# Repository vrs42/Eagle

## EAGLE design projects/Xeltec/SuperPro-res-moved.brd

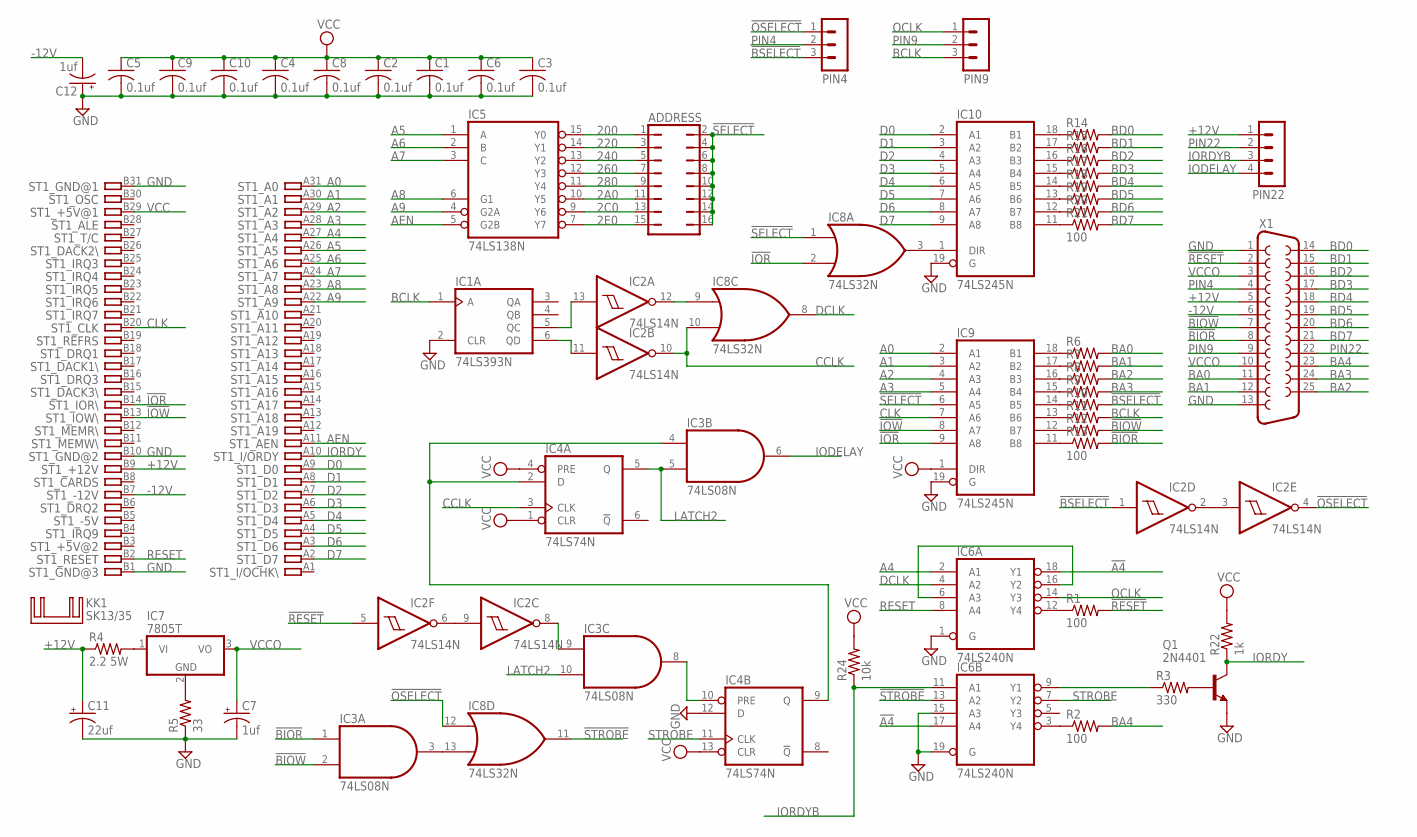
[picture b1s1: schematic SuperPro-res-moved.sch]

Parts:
ADDRESS: JP8Q
C1, C2, C3, C4, C5, C6, C8, C9, C10: 0.1uf; C050-025X075
C7, C12: 1uf; E5-10,5
C11: 22uf; E5-10,5
IC1: 74LS393N; DIL14
IC2: 74LS14N; DIL14
IC3: 74LS08N; DIL14
IC4: 74LS74N; DIL14
IC5: 74LS138N; DIL16
IC6: 74LS240N; DIL20
IC7: 7805T; TO220H
IC8: 74LS32N; DIL14
IC9, IC10: 74LS245N; DIL20
KK1: SK13/35
PIN4, PIN9: MA03-1
PIN22: MA04-1
Q1: 2N4401; TO92
R1, R2, R13, R21: 100; 0207/10
R3: 330; 0207/10
R4: 2.2 5W; 0922/22
R5: 33; 0207/10
R6, R7, R8, R9, R10, R11, R12, R14, R15, R16, R17, R18, R19, R20: R-US_0207/10; 0207/10
R22: 1k; 0207/10
R24: 10k; 0207/10
ST1: IBM8BIT
X1: F25H

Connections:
2A0: ADDRESS.11, IC5.10 (Y5)
2C0: ADDRESS.13, IC5.9 (Y6)
2E0: ADDRESS.15, IC5.7 (Y7)
200: ADDRESS.1, IC5.15 (Y0)
220: ADDRESS.3, IC5.14 (Y1)
240: ADDRESS.5, IC5.13 (Y2)
260: ADDRESS.7, IC5.12 (Y3)
280: ADDRESS.9, IC5.11 (Y4)
!A4: IC6.17 (A4), IC6.18 (Y1)
!BIOR: IC3.1 (I0), R13.2, X1.8
!BIOW: IC3.2 (I1), R12.2, X1.7
!BSELECT: IC2.1 (I), PIN4.3, R10.2
!IOR: IC8.2 (I1), IC9.9 (A8), ST1.B14
!IOW: IC9.8 (A7), ST1.B13
!OSELECT: IC2.4 (O), IC8.12 (I0), PIN4.1
!RESET: IC2.5 (I), R1.2, X1.2
!SELECT: ADDRESS.2, ADDRESS.4, ADDRESS.6, ADDRESS.8, ADDRESS.10, ADDRESS.12, ADDRESS.14, ADDRESS.16, IC8.1 (I0), IC9.6 (A5)
!STROBE: IC6.13 (A2), IC8.11 (O)
+12V: C11.+, PIN22.1, R4.1, ST1.B9, X1.5
-12V: C12.-, ST1.B7, X1.6
A0: IC9.2 (A1), ST1.A31
A1: IC9.3 (A2), ST1.A30
A2: IC9.4 (A3), ST1.A29
A3: IC9.5 (A4), ST1.A28
A4: IC6.2 (A1), ST1.A27
A5: IC5.1 (A), ST1.A26
A6: IC5.2 (B), ST1.A25
A7: IC5.3 (C), ST1.A24
A8: IC5.6 (G1), ST1.A23
A9: IC5.4 (G2A), ST1.A22
AEN: IC5.5 (G2B), ST1.A11
BA0: R6.2, X1.11
BA1: R7.2, X1.12
BA2: R8.2, X1.25
BA3: R9.2, X1.24
BA4: R2.2, X1.23
BCLK: IC1.1 (A), PIN9.3, R11.2
BD0: R14.2, X1.14
BD1: R15.2, X1.15
BD2: R16.2, X1.16
BD3: R17.2, X1.17
BD4: R18.2, X1.18
BD5: R19.2, X1.19
BD6: R20.2, X1.20
BD7: R21.2, X1.21
CCLK: IC2.10 (O), IC4.3 (CLK), IC8.10 (I1)
CLK: IC9.7 (A6), ST1.B20
D0: IC10.2 (A1), ST1.A9
D1: IC10.3 (A2), ST1.A8
D2: IC10.4 (A3), ST1.A7
D3: IC10.5 (A4), ST1.A6
D4: IC10.6 (A5), ST1.A5
D5: IC10.7 (A6), ST1.A4
D6: IC10.8 (A7), ST1.A3
D7: IC10.9 (A8), ST1.A2
DCLK: IC6.4 (A2), IC8.8 (O)
GND: C1.2, C2.2, C3.2, C4.2, C5.2, C6.2, C7.-, C8.2, C9.2, C10.2, C11.-, C12.+, IC1.2 (CLR), IC1.7 (GND), IC2.7 (GND), IC3.7 (GND), IC4.7 (GND), IC4.12 (D), IC5.8 (GND), IC6.1 (G), IC6.10 (GND), IC6.15 (A3), IC6.19 (G), IC8.7 (GND), IC9.10 (GND), IC9.19 (G), IC10.10 (GND), IC10.19 (G), Q1.3 (E), R5.1, ST1.B1, ST1.B10, ST1.B31, X1.1, X1.13
IODELAY: IC3.6 (O), PIN22.4
IORDY: Q1.1 (C), R22.1, ST1.A10
IORDYB: IC6.11 (A1), PIN22.3, R24.1
LATCH2: IC3.5 (I1), IC3.10 (I1), IC4.5 (Q)
unnamed: IC8.3 (O), IC10.1 (DIR)
unnamed: IC7.2 (GND), R5.2
unnamed: IC10.13 (B6), R19.1
unnamed: IC10.17 (B2), R15.1
unnamed: IC10.16 (B3), R16.1
unnamed: IC10.15 (B4), R17.1
unnamed: IC10.14 (B5), R18.1
unnamed: IC10.12 (B7), R20.1
unnamed: IC10.11 (B8), R21.1
unnamed: IC10.18 (B1), R14.1
unnamed: IC9.18 (B1), R6.1
unnamed: IC9.17 (B2), R7.1
unnamed: IC9.16 (B3), R8.1
unnamed: IC9.15 (B4), R9.1
unnamed: IC9.14 (B5), R10.1
unnamed: IC9.13 (B6), R11.1
unnamed: IC9.12 (B7), R12.1
unnamed: IC9.11 (B8), R13.1
unnamed: IC6.12 (Y4), R1.1
unnamed: IC2.6 (O), IC2.9 (I)
unnamed: IC2.2 (O), IC2.3 (I)
unnamed: IC1.6 (QD), IC2.11 (I)
unnamed: IC6.3 (Y4), R2.1
unnamed: IC1.5 (QC), IC2.13 (I)
unnamed: IC7.1 (VI), R4.2
unnamed: IC2.12 (O), IC8.9 (I0)
unnamed: IC6.6 (A3), IC6.16 (Y2)
unnamed: IC3.3 (O), IC8.13 (I1)
unnamed: IC3.4 (I0), IC4.2 (D), IC4.9 (Q)
unnamed: IC6.9 (Y1), R3.1
unnamed: IC3.8 (O), IC4.10 (PRE)
unnamed: IC2.8 (O), IC3.9 (I0)
unnamed: Q1.2 (B), R3.2
OCLK: IC6.14 (Y3), PIN9.1
PIN4: PIN4.2, X1.4
PIN9: PIN9.2, X1.9
PIN22: PIN22.2, X1.22
RESET: IC6.8 (A4), ST1.B2
STROBE: IC4.11 (CLK), IC6.7 (Y2)
VCC: C1.1, C2.1, C3.1, C4.1, C5.1, C6.1, C8.1, C9.1, C10.1, IC1.14 (VCC), IC2.14 (VCC), IC3.14 (VCC), IC4.1 (CLR), IC4.4 (PRE), IC4.13 (CLR), IC4.14 (VCC), IC5.16 (VCC), IC6.20 (VCC), IC8.14 (VCC), IC9.1 (DIR), IC9.20 (VCC), IC10.20 (VCC), R22.2, R24.2, ST1.B29
VCCO: C7.+, IC7.3 (VO), X1.3, X1.10

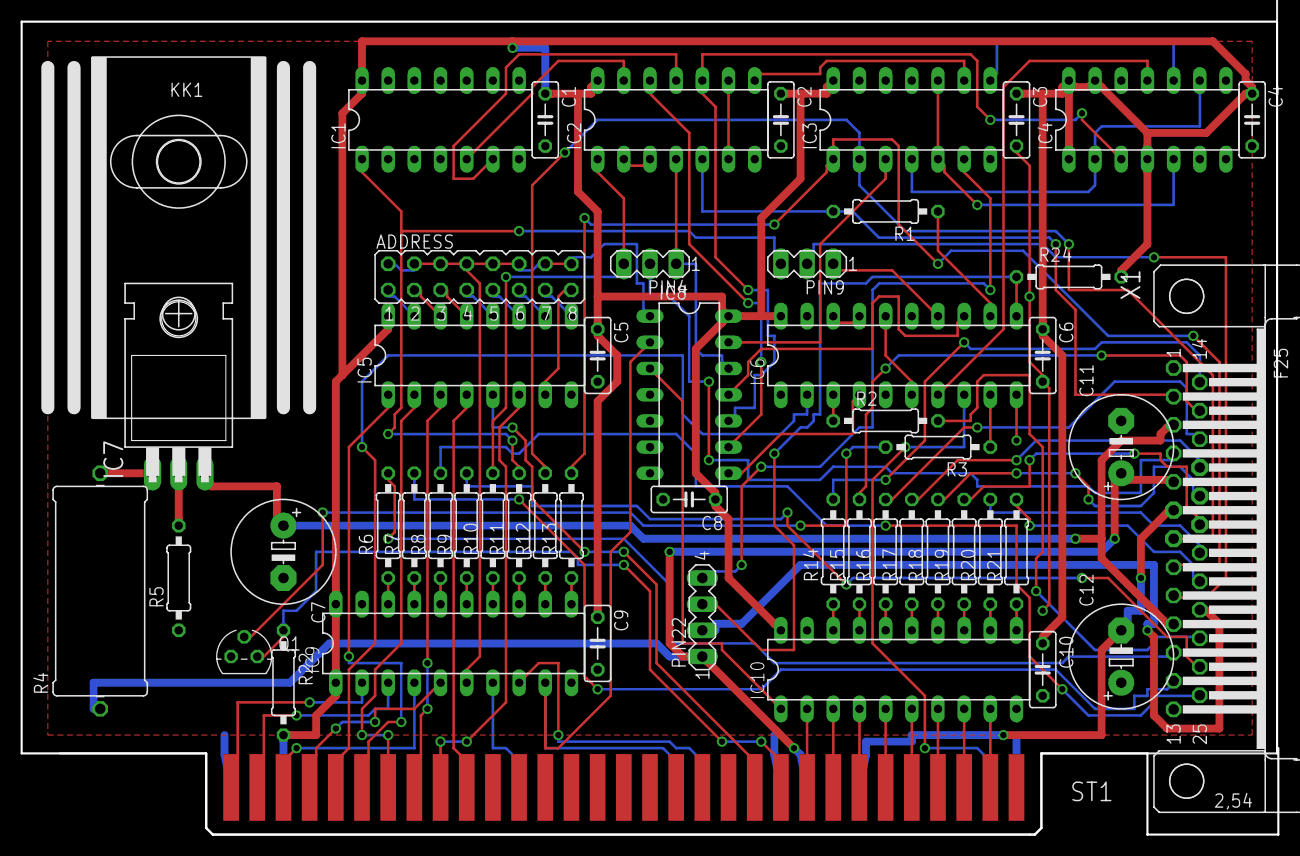
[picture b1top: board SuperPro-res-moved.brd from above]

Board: 2 copper layers, 121.9 x 78.9 mm, 54 parts (0 on the bottom side), 102 nets.

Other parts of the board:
U$1: 4,1

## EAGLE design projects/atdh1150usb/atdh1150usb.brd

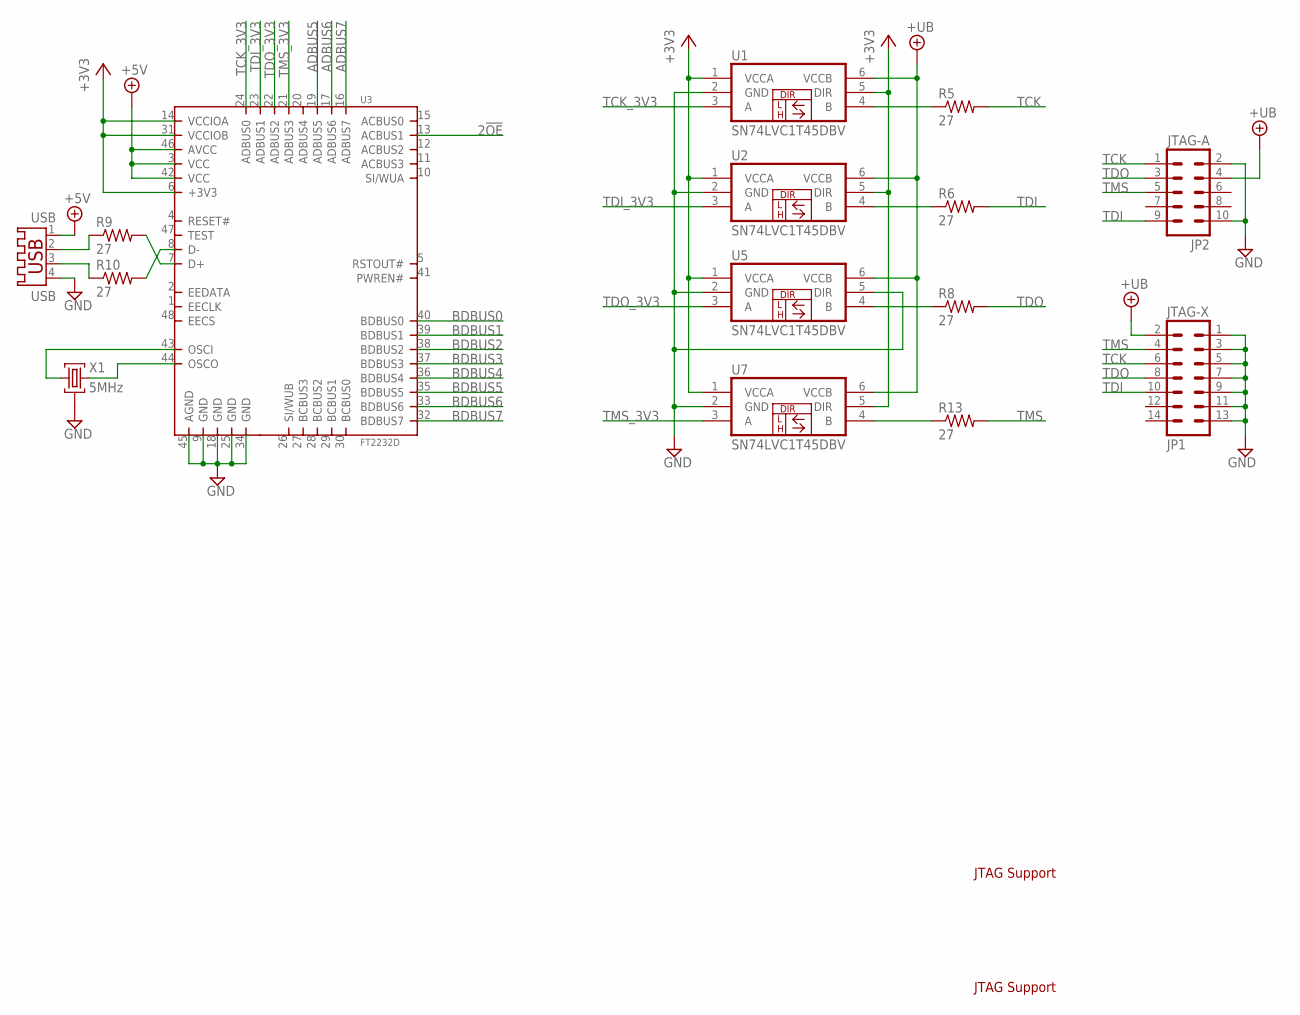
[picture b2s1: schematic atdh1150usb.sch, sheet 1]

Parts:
JP1: JTAG-X; ML14
JP2: JTAG-A; ML10
R5, R6, R8, R9, R10, R13: 27; R0805
U1, U2, U5, U7: SN74LVC1T45DBV; DBV-R-PDSO-G6
U3: FT2232D; LQFP48
USB: USB; USB-A003
X1: 5MHz; HC49U

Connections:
2!OE: U3.13 (ACBUS1); also elsewhere on the board
+3V3: U1.1 (VCCA), U1.5 (DIR), U2.1 (VCCA), U2.5 (DIR), U3.6 (+3V3), U3.14 (VCCIOA), U3.31 (VCCIOB), U5.1 (VCCA), U7.1 (VCCA), U7.5 (DIR); also elsewhere on the board
+5V: U3.3 (VCC), U3.42 (VCC), U3.46 (AVCC), USB.1
+UB: JP1.2, JP2.4, U1.6 (VCCB), U2.6 (VCCB), U5.6 (VCCB), U7.6 (VCCB)
ADBUS5: U3.19 (ADBUS5); also elsewhere on the board
ADBUS6: U3.17 (ADBUS6); also elsewhere on the board
ADBUS7: U3.16 (ADBUS7); also elsewhere on the board
BDBUS0: U3.40 (BDBUS0); also elsewhere on the board
BDBUS1: U3.39 (BDBUS1); also elsewhere on the board
BDBUS2: U3.38 (BDBUS2); also elsewhere on the board
BDBUS3: U3.37 (BDBUS3); also elsewhere on the board
BDBUS4: U3.36 (BDBUS4); also elsewhere on the board
BDBUS5: U3.35 (BDBUS5); also elsewhere on the board
BDBUS6: U3.33 (BDBUS6); also elsewhere on the board
BDBUS7: U3.32 (BDBUS7); also elsewhere on the board
GND: JP1.1, JP1.3, JP1.5, JP1.7, JP1.9, JP1.11, JP1.13, JP2.2, JP2.10, U1.2 (GND), U2.2 (GND), U3.9 (GND), U3.18 (GND), U3.25 (GND), U3.34 (GND), U3.45 (AGND), U5.2 (GND), U5.5 (DIR), U7.2 (GND), USB.4, X1.2; also elsewhere on the board
unnamed: R9.1, USB.2
unnamed: R10.1, USB.3
unnamed: R10.2, U3.8 (D-)
unnamed: R9.2, U3.7 (D+)
unnamed: U3.44 (OSCO), X1.3
unnamed: U3.43 (OSCI), X1.1
unnamed: R5.1, U1.4 (B)
unnamed: R6.1, U2.4 (B)
unnamed: R8.1, U5.4 (B)
unnamed: R13.1, U7.4 (B)
TCK: JP1.6, JP2.1, R5.2
TCK_3V3: U1.3 (A), U3.24 (ADBUS0); also elsewhere on the board
TDI: JP1.10, JP2.9, R6.2
TDI_3V3: U2.3 (A), U3.23 (ADBUS1); also elsewhere on the board
TDO: JP1.8, JP2.3, R8.2
TDO_3V3: U3.22 (ADBUS2), U5.3 (A); also elsewhere on the board
TMS: JP1.4, JP2.5, R13.2
TMS_3V3: U3.21 (ADBUS3), U7.3 (A); also elsewhere on the board

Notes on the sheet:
JTAG Support

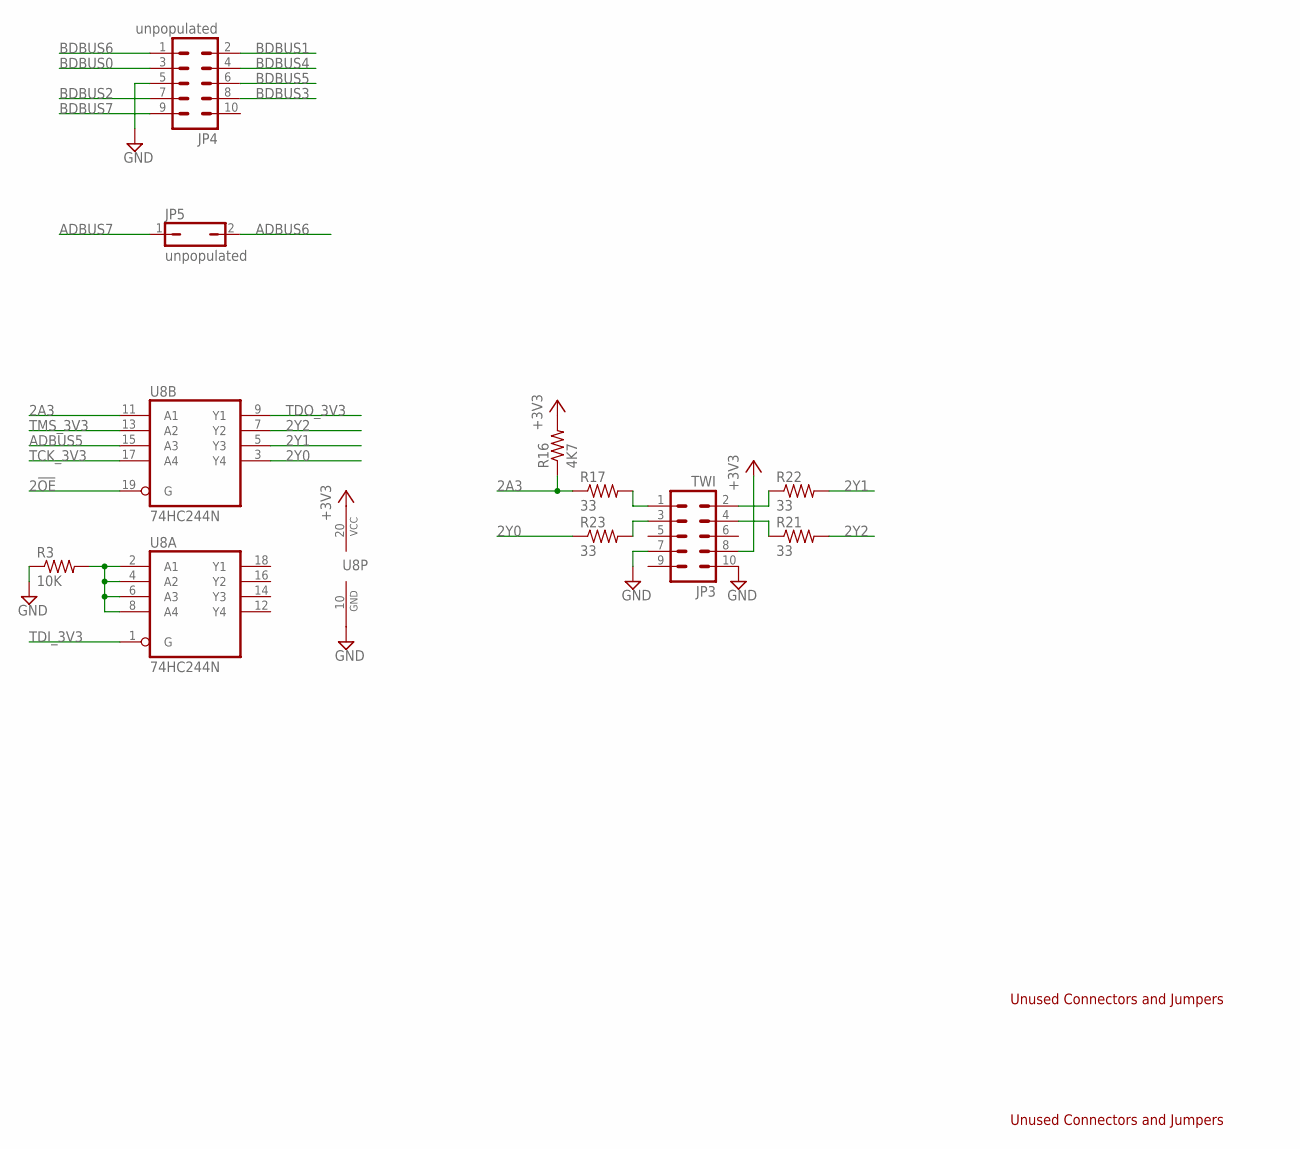
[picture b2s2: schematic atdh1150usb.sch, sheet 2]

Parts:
JP3: TWI; ML10
JP4: unpopulated; ML10
JP5: unpopulated; JP1
R3: 10K; R0805
R16: 4K7; R0805
R17, R21, R22, R23: 33; R0805
U8: 74HC244N; DIL20

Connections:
2!OE: U8.19 (G); also elsewhere on the board
2A3: R16.1, R17.1, U8.11 (A1)
2Y0: R23.1, U8.3 (Y4)
2Y1: R22.2, U8.5 (Y3)
2Y2: R21.2, U8.7 (Y2)
+3V3: JP3.8, R16.2, U8.20 (VCC); also elsewhere on the board
ADBUS5: U8.15 (A3); also elsewhere on the board
ADBUS6: JP5.2; also elsewhere on the board
ADBUS7: JP5.1; also elsewhere on the board
BDBUS0: JP4.3; also elsewhere on the board
BDBUS1: JP4.2; also elsewhere on the board
BDBUS2: JP4.7; also elsewhere on the board
BDBUS3: JP4.8; also elsewhere on the board
BDBUS4: JP4.4; also elsewhere on the board
BDBUS5: JP4.6; also elsewhere on the board
BDBUS6: JP4.1; also elsewhere on the board
BDBUS7: JP4.9; also elsewhere on the board
GND: JP3.7, JP3.10, JP4.5, R3.1, U8.10 (GND); also elsewhere on the board
unnamed: JP3.3, R23.2
unnamed: JP3.1, R17.2
unnamed: R3.2, U8.2 (A1), U8.4 (A2), U8.6 (A3), U8.8 (A4)
unnamed: JP3.2, R22.1
unnamed: JP3.4, R21.1
TCK_3V3: U8.17 (A4); also elsewhere on the board
TDI_3V3: U8.1 (G); also elsewhere on the board
TDO_3V3: U8.9 (Y1); also elsewhere on the board
TMS_3V3: U8.13 (A2); also elsewhere on the board

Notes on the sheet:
Unused Connectors and Jumpers

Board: 2 copper layers, 25 parts (0 on the bottom side), 43 nets, no tracks yet.

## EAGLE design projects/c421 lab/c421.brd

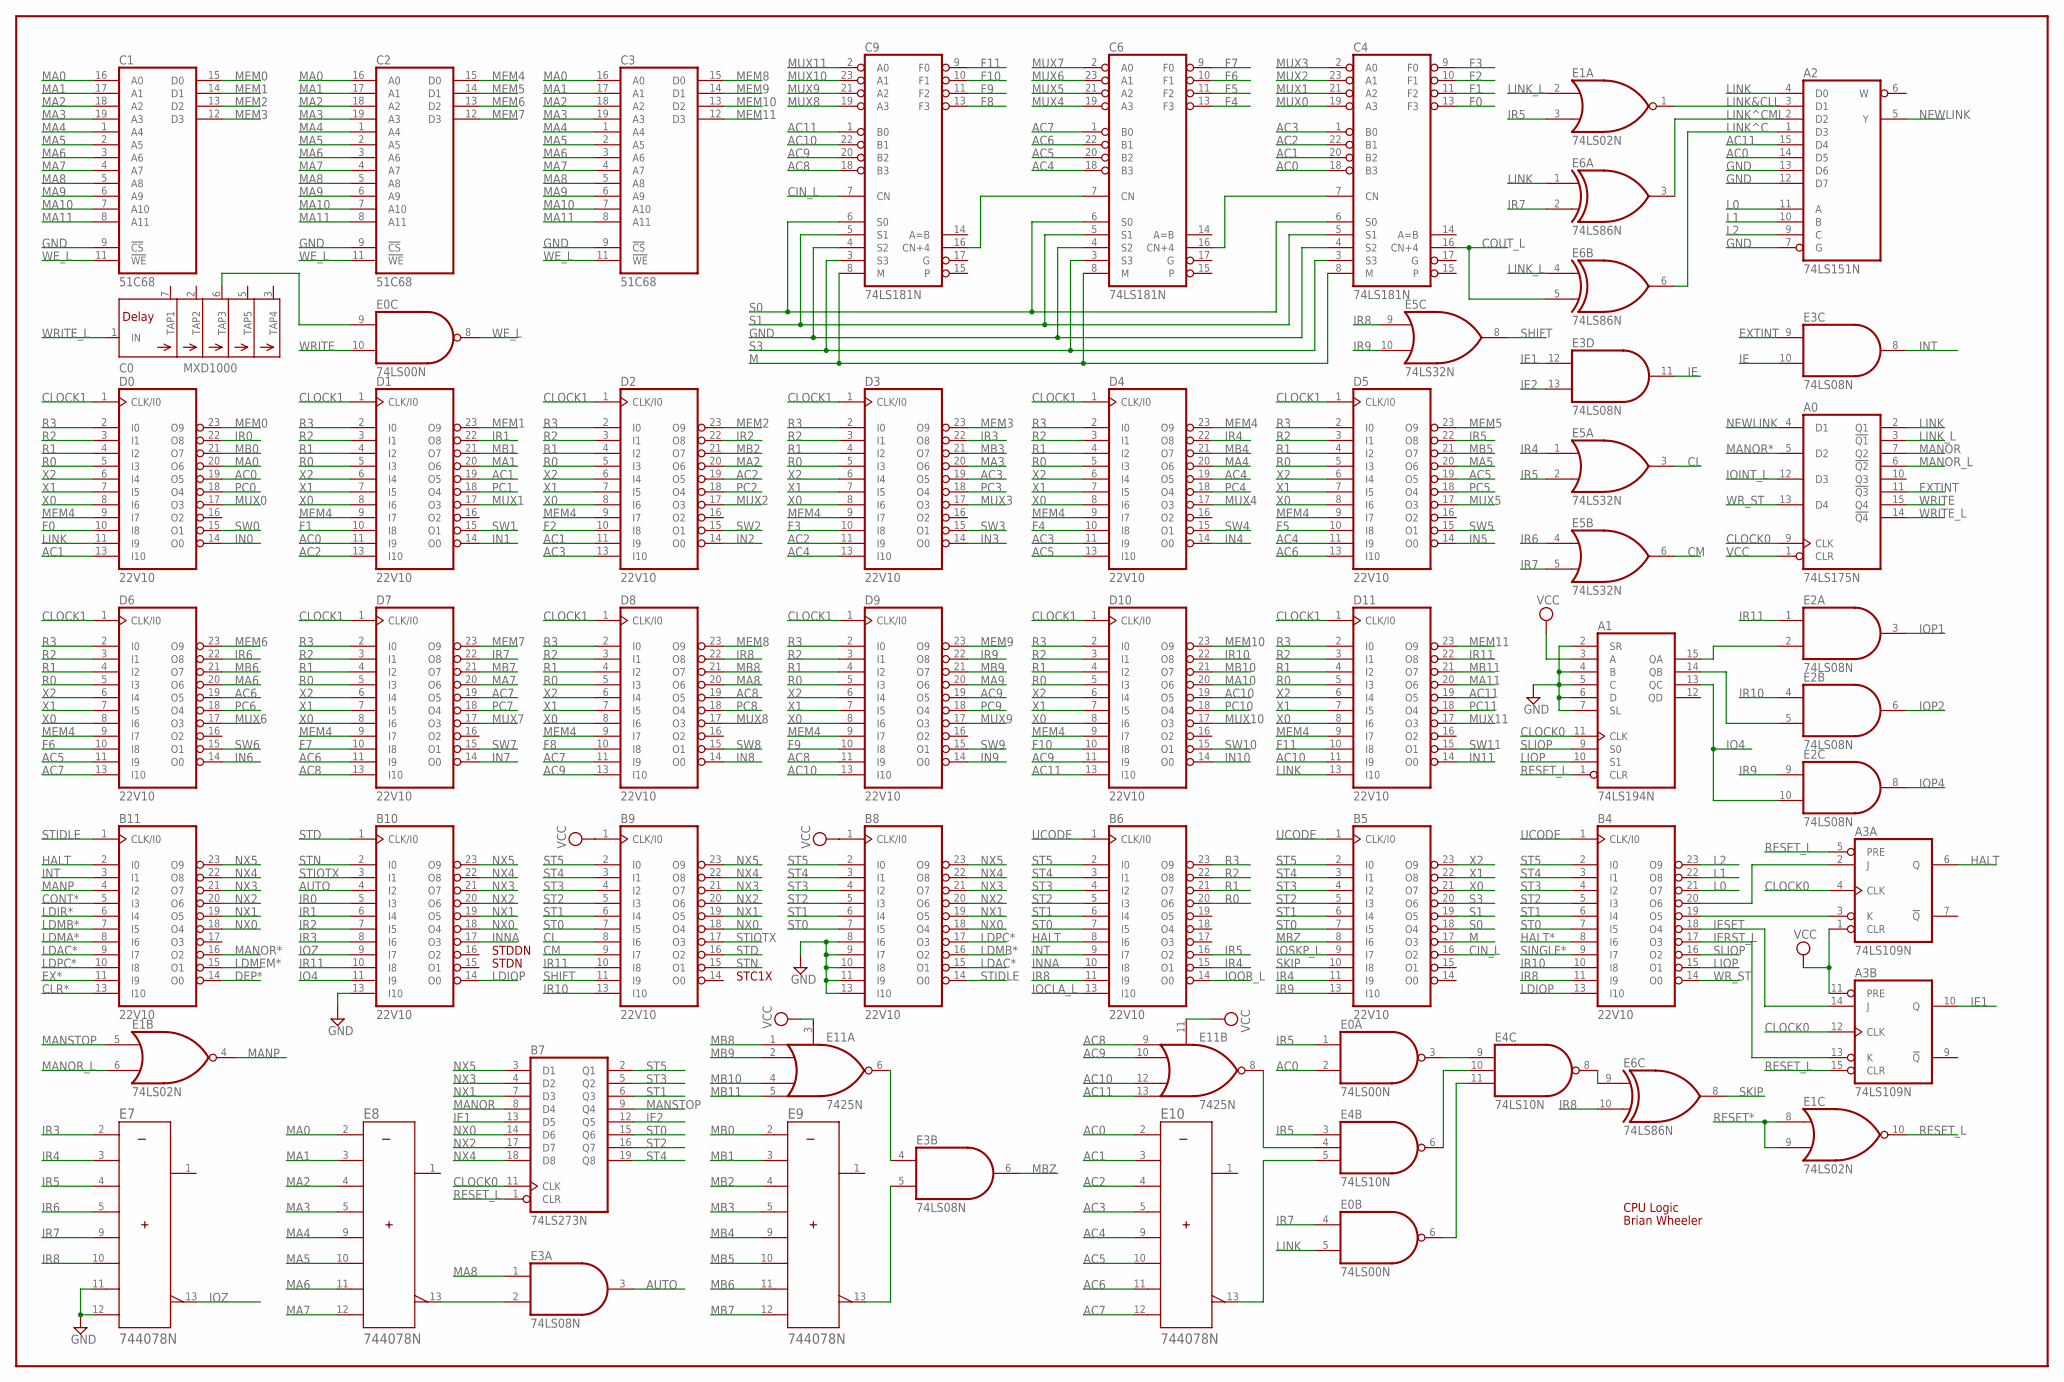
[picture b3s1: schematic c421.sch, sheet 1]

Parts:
A0: 74LS175N; DIL16
A1: 74LS194N; DIL16
A2: 74LS151N; DIL16
A3: 74LS109N; DIL16
B4, B5, B6, B8, B9, B10, B11: 22V10; DIL24-3
B7: 74LS273N; DIL20
C0: MXD1000; DIL08
C1, C2, C3: 51C68; DIL20
C4, C6, C9: 74LS181N; DIL24-6
D0, D1, D2, D3, D4, D5, D6, D7, D8, D9, D10, D11: 22V10; DIL24-3
E0: 74LS00N; DIL14
E1: 74LS02N; DIL14
E2, E3: 74LS08N; DIL14
E4: 74LS10N; DIL14
E5: 74LS32N; DIL14
E6: 74LS86N; DIL14
E7, E8, E9, E10: 744078N; DIL14
E11: 7425N; DIL14

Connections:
AC0: A2.14 (D5), C4.18 (B3), D0.19 (O5), D1.11 (I9), E0.2 (I1), E10.2 (A); also elsewhere on the board
AC1: C4.20 (B2), D0.13 (I10), D1.19 (O5), D2.11 (I9), E10.3 (B); also elsewhere on the board
AC2: C4.22 (B1), D1.13 (I10), D2.19 (O5), D3.11 (I9), E10.4 (C); also elsewhere on the board
AC3: C4.1 (B0), D2.13 (I10), D3.19 (O5), D4.11 (I9), E10.5 (D); also elsewhere on the board
AC4: C6.18 (B3), D3.13 (I10), D4.19 (O5), D5.11 (I9), E10.9 (E); also elsewhere on the board
AC5: C6.20 (B2), D4.13 (I10), D5.19 (O5), D6.11 (I9), E10.10 (F); also elsewhere on the board
AC6: C6.22 (B1), D5.13 (I10), D6.19 (O5), D7.11 (I9), E10.11 (G); also elsewhere on the board
AC7: C6.1 (B0), D6.13 (I10), D7.19 (O5), D8.11 (I9), E10.12 (H); also elsewhere on the board
AC8: C9.18 (B3), D7.13 (I10), D8.19 (O5), D9.11 (I9), E11.9 (I0); also elsewhere on the board
AC9: C9.20 (B2), D8.13 (I10), D9.19 (O5), D10.11 (I9), E11.10 (I1); also elsewhere on the board
AC10: C9.22 (B1), D9.13 (I10), D10.19 (O5), D11.11 (I9), E11.12 (I2); also elsewhere on the board
AC11: A2.15 (D4), C9.1 (B0), D10.13 (I10), D11.19 (O5), E11.13 (I3); also elsewhere on the board
AUTO: B10.4 (I2), E3.3 (O)
CIN_L: B5.16 (O2), C9.7 (CN); also elsewhere on the board
CL: B9.8 (I6), E5.3 (O)
CLOCK0: A0.9 (CLK), A1.11 (CLK), A3.4 (CLK), A3.12 (CLK), B7.11 (CLK); also elsewhere on the board
CLOCK1: D0.1 (CLK/I0), D1.1 (CLK/I0), D2.1 (CLK/I0), D3.1 (CLK/I0), D4.1 (CLK/I0), D5.1 (CLK/I0), D6.1 (CLK/I0), D7.1 (CLK/I0), D8.1 (CLK/I0), D9.1 (CLK/I0), D10.1 (CLK/I0), D11.1 (CLK/I0); also elsewhere on the board
CLR*: B11.13 (I10); also elsewhere on the board
CM: B9.9 (I7), E5.6 (O)
CONT*: B11.5 (I3); also elsewhere on the board
COUT_L: C4.16 (CN+4), E6.5 (I1)
DEP*: B11.14 (O0); also elsewhere on the board
EX*: B11.11 (I9); also elsewhere on the board
EXTINT: A0.11 (!Q3), E3.9 (I0)
F0: C4.13 (F3), D0.10 (I8)
F1: C4.11 (F2), D1.10 (I8)
F2: C4.10 (F1), D2.10 (I8)
F3: C4.9 (F0), D3.10 (I8)
F4: C6.13 (F3), D4.10 (I8)
F5: C6.11 (F2), D5.10 (I8)
F6: C6.10 (F1), D6.10 (I8)
F7: C6.9 (F0), D7.10 (I8)
F8: C9.13 (F3), D8.10 (I8)
F9: C9.11 (F2), D9.10 (I8)
F10: C9.10 (F1), D10.10 (I8)
F11: C9.9 (F0), D11.10 (I8)
GND: A0.8 (GND), A1.2 (SR), A1.4 (B), A1.5 (C), A1.6 (D), A1.7 (SL), A1.8 (GND), A2.7 (G), A2.8 (GND), A2.12 (D7), A2.13 (D6), A3.8 (GND), B4.12 (GND), B5.12 (GND), B6.12 (GND), B7.10 (GND), B8.8 (I6), B8.9 (I7), B8.10 (I8), B8.11 (I9), B8.12 (GND), B8.13 (I10), B9.12 (GND), B10.12 (GND), B10.13 (I10), B11.12 (GND), C0.4 (GND), C1.9 (!CS), C1.10 (GND), C2.9 (!CS), C2.10 (GND), C3.9 (!CS), C3.10 (GND), C4.4 (S2), C4.12 (GND), C6.4 (S2), C6.12 (GND), C9.4 (S2), C9.12 (GND), D0.12 (GND), D1.12 (GND), D2.12 (GND), D3.12 (GND), D4.12 (GND), D5.12 (GND), D6.12 (GND), D7.12 (GND), D8.12 (GND), D9.12 (GND), D10.12 (GND), D11.12 (GND), E0.7 (GND), E1.7 (GND), E2.7 (GND), E3.7 (GND), E4.7 (GND), E5.7 (GND), E6.7 (GND), E7.11 (G), E7.12 (H), E11.7 (GND); also elsewhere on the board
HALT: A3.6 (Q), B6.8 (I6), B11.2 (I0); also elsewhere on the board
HALT*: B4.8 (I6); also elsewhere on the board
IE: E3.10 (I1), E3.11 (O)
IE1: A3.10 (Q), B7.13 (D5), E3.12 (I0)
IE2: B7.12 (Q5), E3.13 (I1)
IERST_L: A3.13 (K), B4.17 (O3)
IESET: A3.14 (J), B4.18 (O4)
IN0: D0.14 (O0); also elsewhere on the board
IN1: D1.14 (O0); also elsewhere on the board
IN2: D2.14 (O0); also elsewhere on the board
IN3: D3.14 (O0); also elsewhere on the board
IN4: D4.14 (O0); also elsewhere on the board
IN5: D5.14 (O0); also elsewhere on the board
IN6: D6.14 (O0); also elsewhere on the board
IN7: D7.14 (O0); also elsewhere on the board
IN8: D8.14 (O0); also elsewhere on the board
IN9: D9.14 (O0); also elsewhere on the board
IN10: D10.14 (O0); also elsewhere on the board
IN11: D11.14 (O0); also elsewhere on the board
INNA: B6.10 (I8), B10.17 (O3)
INT: B6.9 (I7), B11.3 (I1), E3.8 (O)
IO4: A1.13 (QC), B10.11 (I9), E2.10 (I1)
IOCLA_L: B6.13 (I10); also elsewhere on the board
IOINT_L: A0.12 (D3); also elsewhere on the board
IOOR_L: B6.14 (O0); also elsewhere on the board
IOP1: E2.3 (O); also elsewhere on the board
IOP2: E2.6 (O); also elsewhere on the board
IOP4: E2.8 (O); also elsewhere on the board
IOSKP_L: B5.9 (I7); also elsewhere on the board
IOZ: B10.9 (I7), E7.13 (W)
IR0: B10.5 (I3), D0.22 (O8); also elsewhere on the board
IR1: B10.6 (I4), D1.22 (O8); also elsewhere on the board
IR2: B10.7 (I5), D2.22 (O8); also elsewhere on the board
IR3: B10.8 (I6), D3.22 (O8), E7.2 (A); also elsewhere on the board
IR4: B5.11 (I9), B6.15 (O1), D4.22 (O8), E5.1 (I0), E7.3 (B); also elsewhere on the board
IR5: B6.16 (O2), D5.22 (O8), E0.1 (I0), E1.3 (I1), E4.3 (I0), E5.2 (I1), E7.4 (C); also elsewhere on the board
IR6: D6.22 (O8), E5.4 (I0), E7.5 (D); also elsewhere on the board
IR7: D7.22 (O8), E0.4 (I0), E5.5 (I1), E6.2 (I1), E7.9 (E); also elsewhere on the board
IR8: B4.11 (I9), B6.11 (I9), D8.22 (O8), E5.9 (I0), E6.10 (I1), E7.10 (F); also elsewhere on the board
IR9: B5.13 (I10), D9.22 (O8), E2.9 (I0), E5.10 (I1); also elsewhere on the board
IR10: B4.10 (I8), B9.13 (I10), D10.22 (O8), E2.4 (I0); also elsewhere on the board
IR11: B9.10 (I8), B10.10 (I8), D11.22 (O8), E2.1 (I0); also elsewhere on the board
L0: A2.11 (A), B4.21 (O7); also elsewhere on the board
L1: A2.10 (B), B4.22 (O8); also elsewhere on the board
L2: A2.9 (C), B4.23 (O9); also elsewhere on the board
LDAC*: B8.15 (O1), B11.9 (I7); also elsewhere on the board
LDIOP: B4.13 (I10), B10.14 (O0)
LDIR*: B11.6 (I4); also elsewhere on the board
LDMA*: B11.8 (I6); also elsewhere on the board
LDMB*: B8.16 (O2), B11.7 (I5); also elsewhere on the board
LDMEM*: B11.15 (O1); also elsewhere on the board
LDPC*: B8.17 (O3), B11.10 (I8); also elsewhere on the board
LINK: A0.2 (Q1), A2.4 (D0), D0.11 (I9), D11.13 (I10), E0.5 (I1), E6.1 (I0); also elsewhere on the board
LINK&CLL: A2.3 (D1), E1.1 (O)
LINK^C: A2.1 (D3), E6.6 (O)
LINK^CML: A2.2 (D2), E6.3 (O)
LINK_L: A0.3 (!Q1), E1.2 (I0), E6.4 (I0)
LIOP: A1.10 (S1), B4.15 (O1)
M: B5.17 (O3), C4.8 (M), C6.8 (M), C9.8 (M); also elsewhere on the board
MA0: C1.16 (A0), C2.16 (A0), C3.16 (A0), D0.20 (O6), E8.2 (A); also elsewhere on the board
MA1: C1.17 (A1), C2.17 (A1), C3.17 (A1), D1.20 (O6), E8.3 (B); also elsewhere on the board
MA2: C1.18 (A2), C2.18 (A2), C3.18 (A2), D2.20 (O6), E8.4 (C); also elsewhere on the board
MA3: C1.19 (A3), C2.19 (A3), C3.19 (A3), D3.20 (O6), E8.5 (D); also elsewhere on the board
MA4: C1.1 (A4), C2.1 (A4), C3.1 (A4), D4.20 (O6), E8.9 (E); also elsewhere on the board
MA5: C1.2 (A5), C2.2 (A5), C3.2 (A5), D5.20 (O6), E8.10 (F); also elsewhere on the board
MA6: C1.3 (A6), C2.3 (A6), C3.3 (A6), D6.20 (O6), E8.11 (G); also elsewhere on the board
MA7: C1.4 (A7), C2.4 (A7), C3.4 (A7), D7.20 (O6), E8.12 (H); also elsewhere on the board
MA8: C1.5 (A8), C2.5 (A8), C3.5 (A8), D8.20 (O6), E3.1 (I0); also elsewhere on the board
MA9: C1.6 (A9), C2.6 (A9), C3.6 (A9), D9.20 (O6); also elsewhere on the board
MA10: C1.7 (A10), C2.7 (A10), C3.7 (A10), D10.20 (O6); also elsewhere on the board
MA11: C1.8 (A11), C2.8 (A11), C3.8 (A11), D11.20 (O6); also elsewhere on the board
MANOR: A0.7 (Q2), B7.8 (D4)
MANOR*: A0.5 (D2), B11.16 (O2); also elsewhere on the board
MANOR_L: A0.6 (!Q2), E1.6 (I1)
MANP: B11.4 (I2), E1.4 (O)
MANSTOP: B7.9 (Q4), E1.5 (I0)
MB0: D0.21 (O7), E9.2 (A); also elsewhere on the board
MB1: D1.21 (O7), E9.3 (B); also elsewhere on the board
MB2: D2.21 (O7), E9.4 (C); also elsewhere on the board
MB3: D3.21 (O7), E9.5 (D); also elsewhere on the board
MB4: D4.21 (O7), E9.9 (E); also elsewhere on the board
MB5: D5.21 (O7), E9.10 (F); also elsewhere on the board
MB6: D6.21 (O7), E9.11 (G); also elsewhere on the board
MB7: D7.21 (O7), E9.12 (H); also elsewhere on the board
MB8: D8.21 (O7), E11.1 (I0); also elsewhere on the board
MB9: D9.21 (O7), E11.2 (I1); also elsewhere on the board
MB10: D10.21 (O7), E11.4 (I2); also elsewhere on the board
MB11: D11.21 (O7), E11.5 (I3); also elsewhere on the board
MBZ: B5.8 (I6), E3.6 (O)
MEM0: C1.15 (D0), D0.23 (O9); also elsewhere on the board
MEM1: C1.14 (D1), D1.23 (O9); also elsewhere on the board
MEM2: C1.13 (D2), D2.23 (O9); also elsewhere on the board
MEM3: C1.12 (D3), D3.23 (O9); also elsewhere on the board
MEM4: C2.15 (D0), D0.9 (I7), D1.9 (I7), D2.9 (I7), D3.9 (I7), D4.9 (I7), D4.23 (O9), D5.9 (I7), D6.9 (I7), D7.9 (I7), D8.9 (I7), D9.9 (I7), D10.9 (I7), D11.9 (I7); also elsewhere on the board
MEM5: C2.14 (D1), D5.23 (O9); also elsewhere on the board
MEM6: C2.13 (D2), D6.23 (O9); also elsewhere on the board
MEM7: C2.12 (D3), D7.23 (O9); also elsewhere on the board
MEM8: C3.15 (D0), D8.23 (O9); also elsewhere on the board
MEM9: C3.14 (D1), D9.23 (O9); also elsewhere on the board
MEM10: C3.13 (D2), D10.23 (O9); also elsewhere on the board
MEM11: C3.12 (D3), D11.23 (O9); also elsewhere on the board
MUX0: C4.19 (A3), D0.17 (O3)
MUX1: C4.21 (A2), D1.17 (O3)
MUX2: C4.23 (A1), D2.17 (O3)
MUX3: C4.2 (A0), D3.17 (O3)
MUX4: C6.19 (A3), D4.17 (O3)
MUX5: C6.21 (A2), D5.17 (O3)
MUX6: C6.23 (A1), D6.17 (O3)
MUX7: C6.2 (A0), D7.17 (O3)
MUX8: C9.19 (A3), D8.17 (O3)
MUX9: C9.21 (A2), D9.17 (O3)
MUX10: C9.23 (A1), D10.17 (O3)
MUX11: C9.2 (A0), D11.17 (O3)
unnamed: C4.7 (CN), C6.16 (CN+4)
unnamed: E3.2 (I1), E8.13 (W)
unnamed: E4.4 (I1), E11.8 (O)
unnamed: E4.5 (I2), E10.13 (W)
unnamed: E4.8 (O), E6.9 (I0)
unnamed: C0.6 (TAP3), E0.9 (I0)
unnamed: E3.4 (I0), E11.6 (O)
unnamed: E3.5 (I1), E9.13 (W)
unnamed: A1.15 (QA), E2.2 (I1)
unnamed: A1.14 (QB), E2.5 (I1)
unnamed: E0.6 (O), E4.11 (I2)
unnamed: E4.6 (O), E4.10 (I1)
unnamed: E0.3 (O), E4.9 (I0)
unnamed: C6.7 (CN), C9.16 (CN+4)
unnamed: A3.3 (K), B4.19 (O5)
unnamed: A3.2 (J), B4.20 (O6)
NEWLINK: A0.4 (D1), A2.5 (Y)
NX0: B7.14 (D6), B8.18 (O4), B9.18 (O4), B10.18 (O4), B11.18 (O4); also elsewhere on the board
NX1: B7.7 (D3), B8.19 (O5), B9.19 (O5), B10.19 (O5), B11.19 (O5); also elsewhere on the board
NX2: B7.17 (D7), B8.20 (O6), B9.20 (O6), B10.20 (O6), B11.20 (O6); also elsewhere on the board
NX3: B7.4 (D2), B8.21 (O7), B9.21 (O7), B10.21 (O7), B11.21 (O7); also elsewhere on the board
NX4: B7.18 (D8), B8.22 (O8), B9.22 (O8), B10.22 (O8), B11.22 (O8); also elsewhere on the board
NX5: B7.3 (D1), B8.23 (O9), B9.23 (O9), B10.23 (O9), B11.23 (O9); also elsewhere on the board
PC0: D0.18 (O4); also elsewhere on the board
PC1: D1.18 (O4); also elsewhere on the board
PC2: D2.18 (O4); also elsewhere on the board
PC3: D3.18 (O4); also elsewhere on the board
PC4: D4.18 (O4); also elsewhere on the board
PC5: D5.18 (O4); also elsewhere on the board
PC6: D6.18 (O4); also elsewhere on the board
PC7: D7.18 (O4); also elsewhere on the board
PC8: D8.18 (O4); also elsewhere on the board
PC9: D9.18 (O4); also elsewhere on the board
PC10: D10.18 (O4); also elsewhere on the board
PC11: D11.18 (O4); also elsewhere on the board
R0: B6.20 (O6), D0.5 (I3), D1.5 (I3), D2.5 (I3), D3.5 (I3), D4.5 (I3), D5.5 (I3), D6.5 (I3), D7.5 (I3), D8.5 (I3), D9.5 (I3), D10.5 (I3), D11.5 (I3); also elsewhere on the board
R1: B6.21 (O7), D0.4 (I2), D1.4 (I2), D2.4 (I2), D3.4 (I2), D4.4 (I2), D5.4 (I2), D6.4 (I2), D7.4 (I2), D8.4 (I2), D9.4 (I2), D10.4 (I2), D11.4 (I2); also elsewhere on the board
R2: B6.22 (O8), D0.3 (I1), D1.3 (I1), D2.3 (I1), D3.3 (I1), D4.3 (I1), D5.3 (I1), D6.3 (I1), D7.3 (I1), D8.3 (I1), D9.3 (I1), D10.3 (I1), D11.3 (I1); also elsewhere on the board
R3: B6.23 (O9), D0.2 (I0), D1.2 (I0), D2.2 (I0), D3.2 (I0), D4.2 (I0), D5.2 (I0), D6.2 (I0), D7.2 (I0), D8.2 (I0), D9.2 (I0), D10.2 (I0), D11.2 (I0); also elsewhere on the board
RESET*: E1.8 (I0), E1.9 (I1); also elsewhere on the board
RESET_L: A1.1 (CLR), A3.5 (PRE), A3.15 (CLR), B7.1 (CLR), E1.10 (O)
S0: B5.18 (O4), C4.6 (S0), C6.6 (S0), C9.6 (S0); also elsewhere on the board
S1: B5.19 (O5), C4.5 (S1), C6.5 (S1), C9.5 (S1); also elsewhere on the board
S3: B5.20 (O6), C4.3 (S3), C6.3 (S3), C9.3 (S3); also elsewhere on the board
SHIFT: B9.11 (I9), E5.8 (O)
SINGLE*: B4.9 (I7); also elsewhere on the board
SKIP: B5.10 (I8), E6.8 (O)
SLIOP: A1.9 (S0), B4.16 (O2)
ST0: B4.7 (I5), B5.7 (I5), B6.7 (I5), B7.15 (Q6), B8.7 (I5), B9.7 (I5); also elsewhere on the board
ST1: B4.6 (I4), B5.6 (I4), B6.6 (I4), B7.6 (Q3), B8.6 (I4), B9.6 (I4); also elsewhere on the board
ST2: B4.5 (I3), B5.5 (I3), B6.5 (I3), B7.16 (Q7), B8.5 (I3), B9.5 (I3); also elsewhere on the board
ST3: B4.4 (I2), B5.4 (I2), B6.4 (I2), B7.5 (Q2), B8.4 (I2), B9.4 (I2); also elsewhere on the board
ST4: B4.3 (I1), B5.3 (I1), B6.3 (I1), B7.19 (Q8), B8.3 (I1), B9.3 (I1); also elsewhere on the board
ST5: B4.2 (I0), B5.2 (I0), B6.2 (I0), B7.2 (Q1), B8.2 (I0), B9.2 (I0); also elsewhere on the board
STD: B9.16 (O2), B10.1 (CLK/I0)
STIDLE: B8.14 (O0), B11.1 (CLK/I0)
STIOTX: B9.17 (O3), B10.3 (I1)
STN: B9.15 (O1), B10.2 (I0)
SW0: D0.15 (O1); also elsewhere on the board
SW1: D1.15 (O1); also elsewhere on the board
SW2: D2.15 (O1); also elsewhere on the board
SW3: D3.15 (O1); also elsewhere on the board
SW4: D4.15 (O1); also elsewhere on the board
SW5: D5.15 (O1); also elsewhere on the board
SW6: D6.15 (O1); also elsewhere on the board
SW7: D7.15 (O1); also elsewhere on the board
SW8: D8.15 (O1); also elsewhere on the board
SW9: D9.15 (O1); also elsewhere on the board
SW10: D10.15 (O1); also elsewhere on the board
SW11: D11.15 (O1); also elsewhere on the board
UCODE: B4.1 (CLK/I0), B5.1 (CLK/I0), B6.1 (CLK/I0); also elsewhere on the board
VCC: A0.1 (CLR), A0.16 (VCC), A1.3 (A), A1.16 (VCC), A2.16 (VCC), A3.1 (CLR), A3.11 (PRE), A3.16 (VCC), B4.24 (VCC), B5.24 (VCC), B6.24 (VCC), B7.20 (VCC), B8.1 (CLK/I0), B8.24 (VCC), B9.1 (CLK/I0), B9.24 (VCC), B10.24 (VCC), B11.24 (VCC), C0.8 (VCC), C1.20 (VCC), C2.20 (VCC), C3.20 (VCC), C4.24 (VCC), C6.24 (VCC), C9.24 (VCC), D0.24 (VCC), D1.24 (VCC), D2.24 (VCC), D3.24 (VCC), D4.24 (VCC), D5.24 (VCC), D6.24 (VCC), D7.24 (VCC), D8.24 (VCC), D9.24 (VCC), D10.24 (VCC), D11.24 (VCC), E0.14 (VCC), E1.14 (VCC), E2.14 (VCC), E3.14 (VCC), E4.14 (VCC), E5.14 (VCC), E6.14 (VCC), E11.3 (G), E11.11 (G), E11.14 (VCC); also elsewhere on the board
WE_L: C1.11 (!WE), C2.11 (!WE), C3.11 (!WE), E0.8 (O)
WRITE: A0.15 (Q4), E0.10 (I1)
WRITE_L: A0.14 (!Q4), C0.1 (IN)
WR_ST: A0.13 (D4), B4.14 (O0)
X0: B5.21 (O7), D0.8 (I6), D1.8 (I6), D2.8 (I6), D3.8 (I6), D4.8 (I6), D5.8 (I6), D6.8 (I6), D7.8 (I6), D8.8 (I6), D9.8 (I6), D10.8 (I6), D11.8 (I6); also elsewhere on the board
X1: B5.22 (O8), D0.7 (I5), D1.7 (I5), D2.7 (I5), D3.7 (I5), D4.7 (I5), D5.7 (I5), D6.7 (I5), D7.7 (I5), D8.7 (I5), D9.7 (I5), D10.7 (I5), D11.7 (I5); also elsewhere on the board
X2: B5.23 (O9), D0.6 (I4), D1.6 (I4), D2.6 (I4), D3.6 (I4), D4.6 (I4), D5.6 (I4), D6.6 (I4), D7.6 (I4), D8.6 (I4), D9.6 (I4), D10.6 (I4), D11.6 (I4); also elsewhere on the board

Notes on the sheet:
STDDN
STDN
STC1X
CPU Logic
Brian Wheeler

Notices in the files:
projects/df32 emul/DEC8L-buscon.brd:
DEC-8/L Posibus Connector Rev.A (c)2003 CEMorris
